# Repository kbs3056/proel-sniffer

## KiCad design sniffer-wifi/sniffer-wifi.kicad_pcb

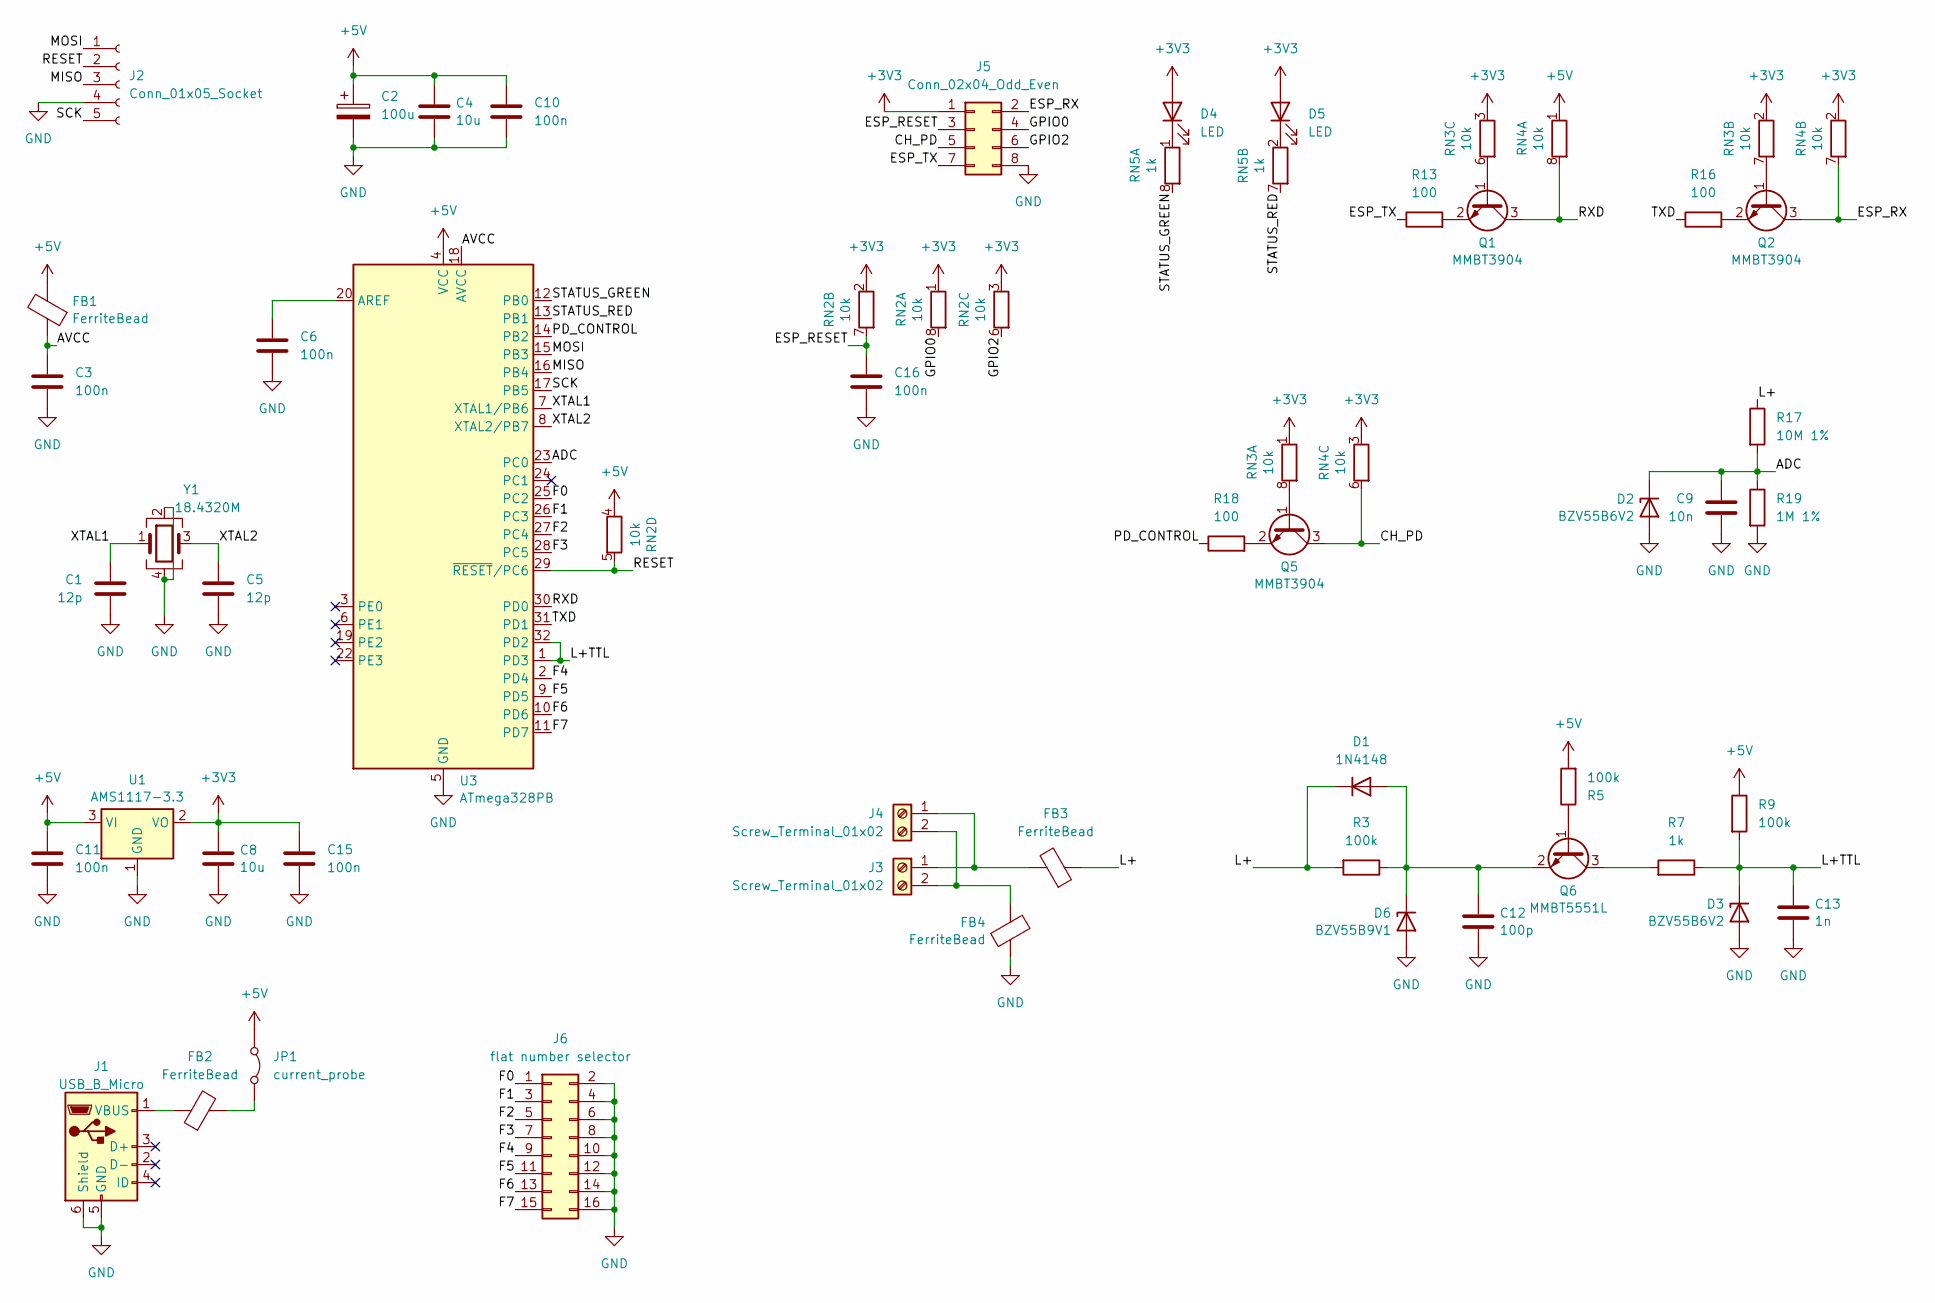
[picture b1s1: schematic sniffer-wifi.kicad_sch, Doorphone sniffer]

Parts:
C1, C5: 12p; C_0805_2012Metric
C2: 100u; CP_Elec_6.3x9.9
C3, C6, C10, C11, C15, C16: 100n; C_0805_2012Metric
C4, C8: 10u; C_1206_3216Metric
C9: 10n; C_0805_2012Metric
C12: 100p; C_0805_2012Metric
C13: 1n; C_0805_2012Metric
D1: 1N4148; D_MiniMELF
D2, D3: BZV55B6V2; D_MiniMELF
D4, D5: LED; LED_0805_2012Metric
D6: BZV55B9V1; D_MiniMELF
FB1, FB2, FB3, FB4: FerriteBead; L_0805_2012Metric
J1: USB_B_Micro; USB_Micro-B
J2: Conn_01x05_Socket; PinHeader_1x05_P2.54mm_Vertical
J3, J4: Screw_Terminal_01x02; TerminalBlock_bornier-2_P5.08mm
J5: Conn_02x04_Odd_Even; PinSocket_2x04_P2.54mm_Vertical
J6: flat number selector; PinHeader_2x08_P2.54mm_Vertical
JP1: current_probe; PinHeader_1x02_P2.54mm_Vertical
Q1, Q2, Q5: MMBT3904; SOT-23
Q6: MMBT5551L; SOT-23
R3: 100k; R_1206_3216Metric
R5, R9: 100k; R_0805_2012Metric
R7: 1k; R_0805_2012Metric
R13, R16, R18: 100; R_0603_1608Metric
R17: 10M 1%; R_1206_3216Metric
R19: 1M 1%; R_1206_3216Metric
RN2, RN3, RN4: 10k; R_Array_Convex_4x0603
RN5: 1k; R_Array_Convex_4x0603
U1: AMS1117-3.3; SOT-223-3_TabPin2
U3: ATmega328PB; TQFP-32_7x7mm_P0.8mm
Y1: 18.4320M; Crystal_SMD_3225-4Pin_3.2x2.5mm

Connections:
+3V3: C8.1, C15.1, D4.2 (A), D5.2 (A), J5.1, RN2.1 (R1.1), RN2.2 (R2.1), RN2.3 (R3.1), RN3.1 (R1.1), RN3.2 (R2.1), RN3.3 (R3.1), RN4.2 (R2.1), RN4.3 (R3.1), U1.2 (VO)
+5V: C2.1, C4.1, C10.1, C11.1, FB1.2, JP1.1 (A), R5.2, R9.1, RN2.4 (R4.1), RN4.1 (R1.1), U1.3 (VI), U3.4 (VCC)
/ADC: C9.1, D2.1 (K), R17.2, R19.1, U3.23 (PC0)
/AVCC: C3.1, FB1.1, U3.18 (AVCC)
/CH_PD: J5.5, Q5.3 (C), RN4.6 (R3.2)
/ESP_RESET: C16.1, J5.3, RN2.7 (R2.2)
/ESP_RX: J5.2, Q2.3 (C), RN4.7 (R2.2)
/ESP_TX: J5.7, R13.1
/F0: J6.1, U3.25 (PC2)
/F1: J6.3, U3.26 (PC3)
/F2: J6.5, U3.27 (PC4)
/F3: J6.7, U3.28 (PC5)
/F4: J6.9, U3.2 (PD4)
/F5: J6.11, U3.9 (PD5)
/F6: J6.13, U3.10 (PD6)
/F7: J6.15, U3.11 (PD7)
/GPIO0: J5.4, RN2.8 (R1.2)
/GPIO2: J5.6, RN2.6 (R3.2)
/L+: D1.1 (K), FB3.1, R3.2, R17.1
/L+TTL: C13.1, D3.1 (K), R7.1, R9.2, U3.1 (PD3), U3.32 (PD2)
/MISO: J2.3, U3.16 (PB4)
/MOSI: J2.1, U3.15 (PB3)
/PD_CONTROL: R18.1, U3.14 (PB2)
/RESET: J2.2, RN2.5 (R4.2), U3.29 (~RESET/PC6)
/RXD: Q1.3 (C), RN4.8 (R1.2), U3.30 (PD0)
/SCK: J2.5, U3.17 (PB5)
/STATUS_GREEN: RN5.8 (R1.2), U3.12 (PB0)
/STATUS_RED: RN5.7 (R2.2), U3.13 (PB1)
/TXD: R16.1, U3.31 (PD1)
/XTAL1: C1.1, U3.7 (XTAL1/PB6), Y1.1
/XTAL2: C5.1, U3.8 (XTAL2/PB7), Y1.3
GND: C1.2, C2.2, C3.2, C4.2, C5.2, C6.2, C8.2, C9.2, C10.2, C11.2, C12.2, C13.2, C15.2, C16.2, D2.2 (A), D3.2 (A), D6.2 (A), FB4.1, J1.5 (GND), J1.6 (Shield), J2.4, J5.8, J6.2, J6.4, J6.6, J6.8, J6.10, J6.12, J6.14, J6.16, R19.2, U1.1 (GND), U3.5 (GND), U3.21 (GND), Y1.2, Y1.4
unnamed: C12.1, D1.2 (A), D6.1 (K), Q6.2 (E), R3.1
unnamed: D4.1 (K), RN5.1 (R1.1)
unnamed: D5.1 (K), RN5.2 (R2.1)
unnamed: FB2.1, J1.1 (VBUS)
unnamed: FB3.2, J3.1, J4.1
unnamed: FB4.2, J3.2, J4.2
unnamed: FB2.2, JP1.2 (B)
unnamed: Q1.1 (B), RN3.6 (R3.2)
unnamed: Q1.2 (E), R13.2
unnamed: Q2.1 (B), RN3.7 (R2.2)
unnamed: Q2.2 (E), R16.2
unnamed: Q5.1 (B), RN3.8 (R1.2)
unnamed: Q5.2 (E), R18.2
unnamed: Q6.1 (B), R5.1
unnamed: Q6.3 (C), R7.2
unnamed: C6.1, U3.20 (AREF)

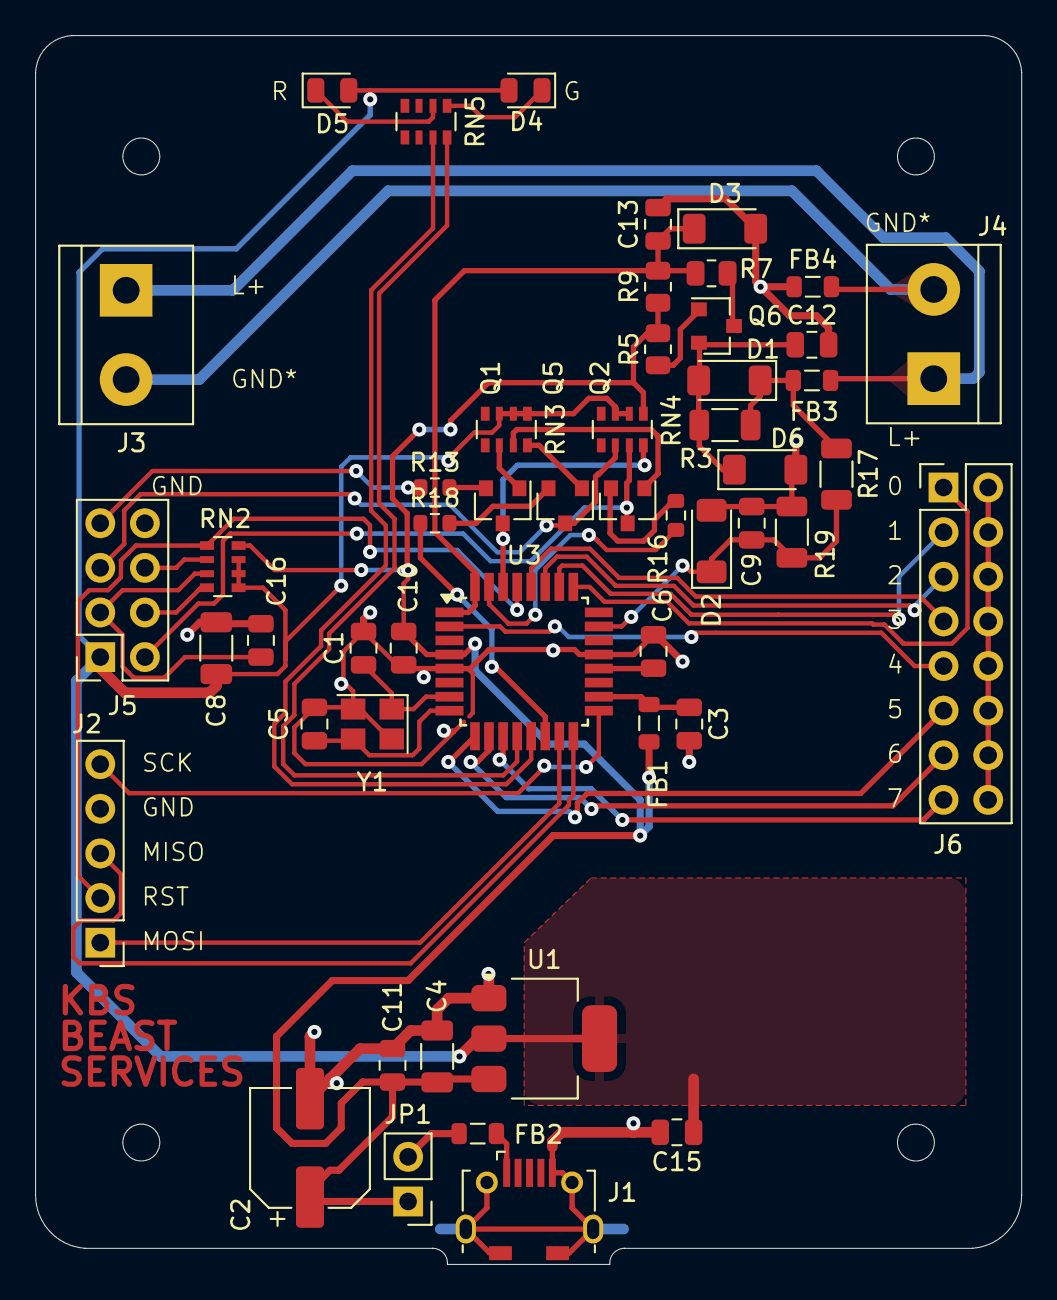
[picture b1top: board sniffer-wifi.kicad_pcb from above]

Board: 2 copper layers, 56.1 x 70.0 mm, 55 parts (0 on the bottom side), 48 nets.

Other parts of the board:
REF1, REF2, REF3, REF4: MountingHole_2.1mm

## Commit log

2024-11-15 Add PCB design
2024-11-15 Add schematic pdf
